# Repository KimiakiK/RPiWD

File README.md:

# R RPiWD - 小型対面対戦ゲーム機 -

RPiWD(ラズパイダブルディスプレイ)はRaspberry Pi Zeroに取り付けてゲームが遊べる HATです。

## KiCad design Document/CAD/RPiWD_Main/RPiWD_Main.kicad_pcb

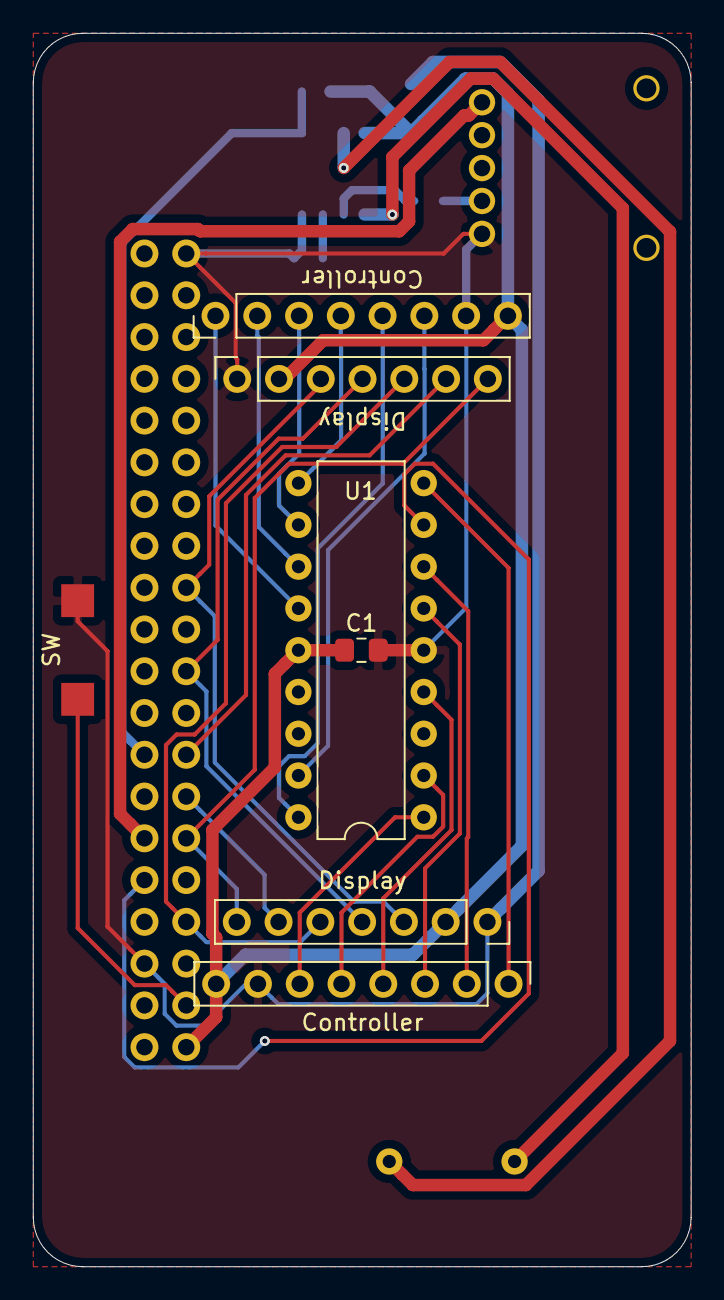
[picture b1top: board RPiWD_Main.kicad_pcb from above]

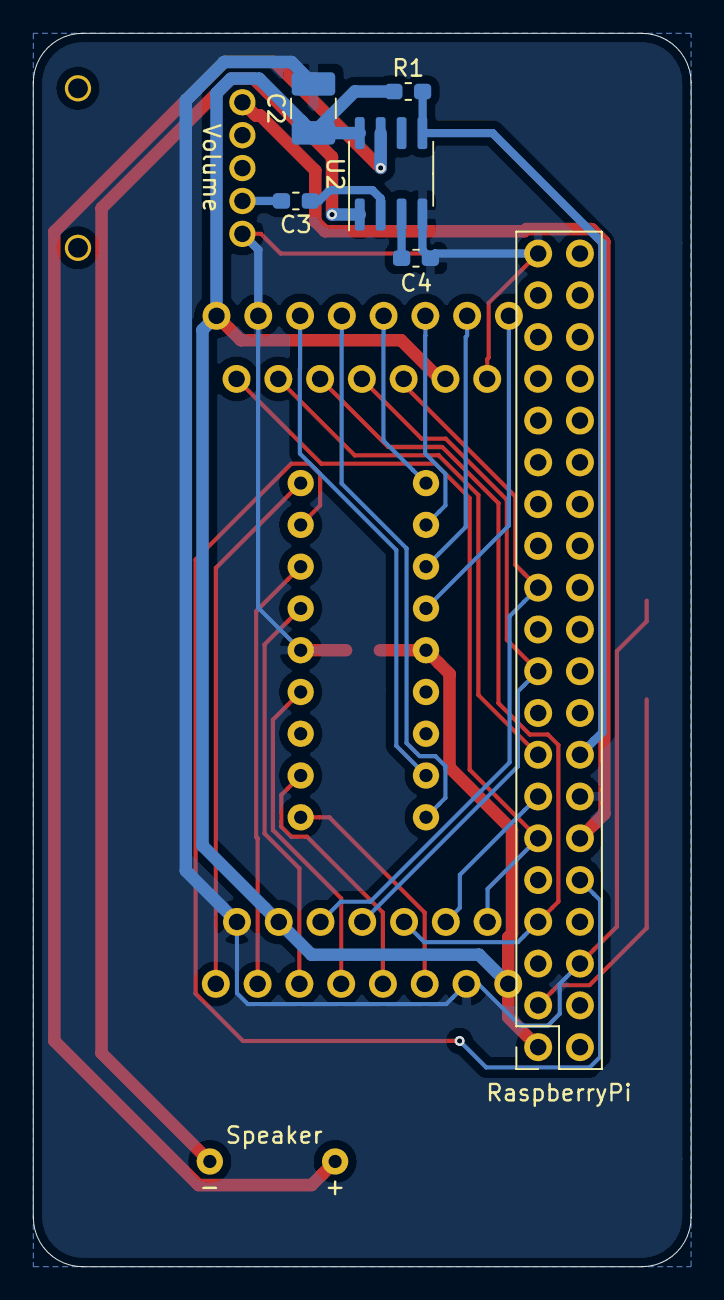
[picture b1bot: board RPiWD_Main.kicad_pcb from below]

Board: 2 copper layers, 40.0 x 75.0 mm, 15 parts (8 on the bottom side), 29 nets.

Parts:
C1: 0.1u; C_0805_2012Metric_Pad1.15x1.40mm_HandSolder
C2: 47u; C_1210_3225Metric_Pad1.42x2.65mm_HandSolder
C3, C4: 1u; C_0603_1608Metric_Pad1.05x0.95mm_HandSolder
Controller: Controller1; PinHeader_1x08_P2.54mm_Vertical
Controller#2: Controller2; PinHeader_1x08_P2.54mm_Vertical
Display: TFT; PinSocket_1x07_P2.54mm_Vertical
Display#2: TFT_1_3_inch; PinSocket_1x07_P2.54mm_Vertical
R1: 10k; R_0603_1608Metric_Pad1.05x0.95mm_HandSolder
RaspberryPi: Raspberry_Pi_Zero; PinSocket_2x20_P2.54mm_Vertical
SW: SW_Push; Switch_TS665SG-S
Speaker: Speaker; Speaker_SP-281W
U1: PIC16F1827; DIP-18_W7.62mm
U2: HT82V739; SOIC-8_3.9x4.9mm_P1.27mm
Volume: Vol; Volume_RK10J

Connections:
+3V3: C1.1, C2.1, Controller.8, Controller#2.8, Display.2, Display#2.2, R1.1, RaspberryPi.1, U1.14, U2.8
GND: C1.2, C2.2, C4.2, Controller.7, Controller#2.7, Display.1, Display#2.1, RaspberryPi.6, RaspberryPi.14, RaspberryPi.39, SW.1, U1.5, U2.4, Volume.1
unnamed: C3.1, U2.2
unnamed: C3.2, Volume.2
unnamed: C4.1, U2.3
unnamed: RaspberryPi.3, SW.2
unnamed: Display.5, Display#2.5, RaspberryPi.7
unnamed: RaspberryPi.10, U1.8
unnamed: Display.7, Display#2.7, RaspberryPi.11
unnamed: RaspberryPi.12, Volume.3
unnamed: Display.6, RaspberryPi.13
unnamed: Display#2.6, RaspberryPi.15
unnamed: R1.2, RaspberryPi.16, U2.5
unnamed: Display.4, Display#2.4, RaspberryPi.19
unnamed: Display.3, Display#2.3, RaspberryPi.23
unnamed: Controller.1, U1.9
unnamed: Controller.2, U1.7
unnamed: Controller.3, U1.6
unnamed: Controller.4, U1.4
unnamed: Controller.5, U1.2
unnamed: Controller.6, U1.1
unnamed: Controller#2.1, U1.13
unnamed: Controller#2.2, U1.12
unnamed: Controller#2.3, U1.11
unnamed: Controller#2.4, U1.10
unnamed: Controller#2.5, U1.18
unnamed: Controller#2.6, U1.17
unnamed: Speaker.1, U2.1
unnamed: Speaker.2, U2.7

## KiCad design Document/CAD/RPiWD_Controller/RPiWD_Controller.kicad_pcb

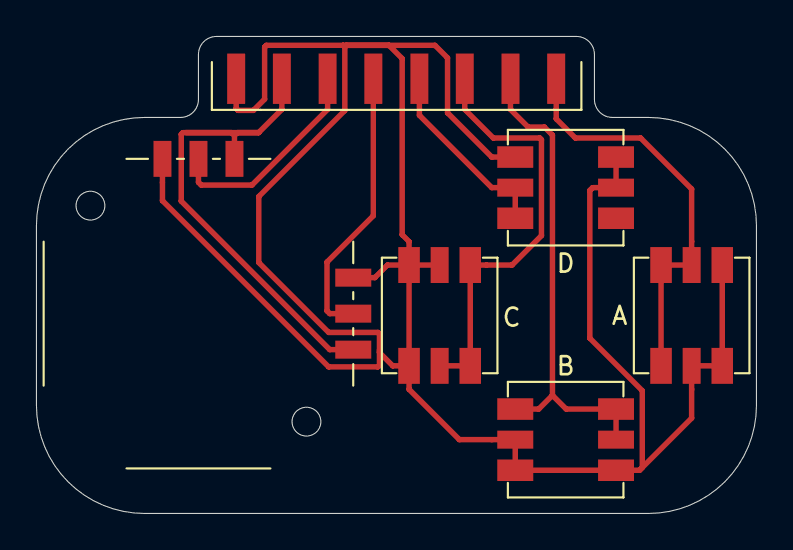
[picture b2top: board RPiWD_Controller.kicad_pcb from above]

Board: 2 copper layers, 40.0 x 26.5 mm, 6 parts (0 on the bottom side), 8 nets.

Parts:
J1: Connector; Connecter_SMD_8pin
RV1: AnalogJoyStick
SW1: SW1; SW_SMD
SW2: SW2; SW_SMD
SW3: SW3; SW_SMD
SW4: SW4; SW_SMD

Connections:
GND: J1.1, RV1.3, RV1.6, SW1.2, SW2.2, SW3.2, SW4.2
unnamed: J1.3, RV1.2
unnamed: J1.4, RV1.5
unnamed: J1.5, SW4.1
unnamed: J1.6, SW3.1
unnamed: J1.7, SW2.1
unnamed: J1.8, SW1.1
VPP: J1.2, RV1.1, RV1.4

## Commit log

2019-08-10 コントローラ動作確認用ソフト
2019-08-31 ブロック図、回路図、パーツリストを追加
2019-09-01 起動用スクリプト追加
2019-09-09 ソフトウェアDFD追加
2019-09-09 写真追加
2020-01-11 PCB版の写真追加
2020-01-11 CADデータ追加
